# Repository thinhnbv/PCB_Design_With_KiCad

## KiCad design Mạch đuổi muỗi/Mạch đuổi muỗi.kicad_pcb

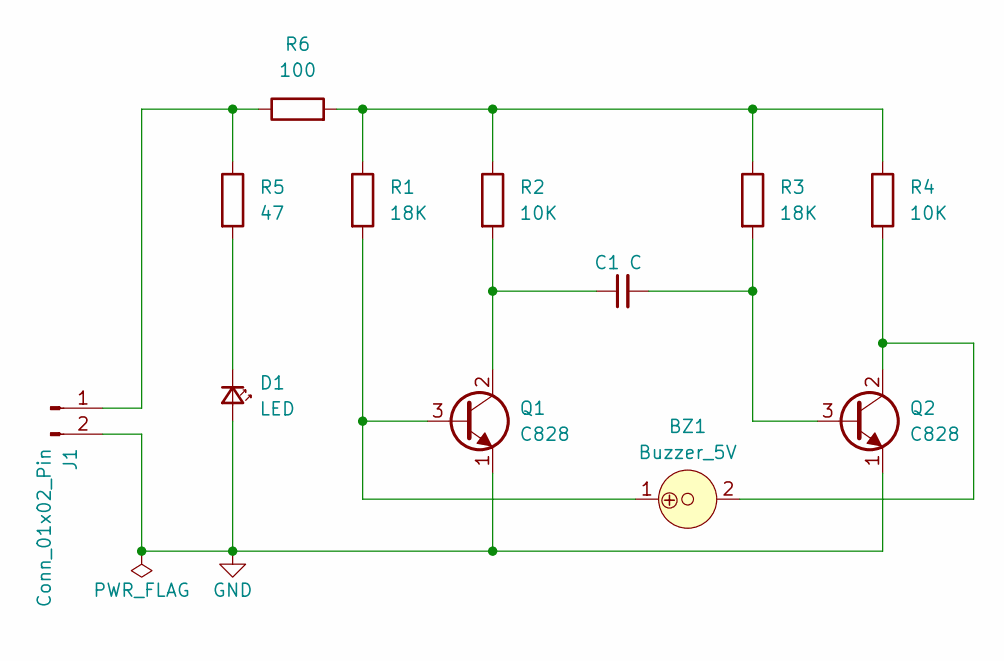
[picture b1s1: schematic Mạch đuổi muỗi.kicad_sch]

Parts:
BZ1: Buzzer_5V; MagneticBuzzer_ProSignal_ABT-410-RC
C1: C; C_Radial_D5.0mm_H5.0mm_P2.00mm; Voltage 1kV; Tolerance 100%
D1: LED; LED_D3.0mm
J1: Conn_01x02_Pin; PinHeader_1x02_P1.27mm_Horizontal
Q1, Q2: C828; TO-92_Inline_Wide
R1, R3: 18K; R_Axial_DIN0207_L6.3mm_D2.5mm_P7.62mm_Horizontal
R2, R4: 10K; R_Axial_DIN0207_L6.3mm_D2.5mm_P7.62mm_Horizontal
R5: 47; R_Axial_DIN0207_L6.3mm_D2.5mm_P7.62mm_Horizontal
R6: 100; R_Axial_DIN0207_L6.3mm_D2.5mm_P7.62mm_Horizontal

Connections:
GND: D1.2 (A), J1.2, Q1.1, Q2.1
unnamed: BZ1.1, Q1.3, R1.2
unnamed: BZ1.2, Q2.2, R4.2
unnamed: C1.1, Q1.2, R2.2
unnamed: C1.2, Q2.3, R3.2
unnamed: D1.1 (K), R5.2
unnamed: J1.1, R5.1, R6.1
unnamed: R1.1, R2.1, R3.1, R4.1, R6.2

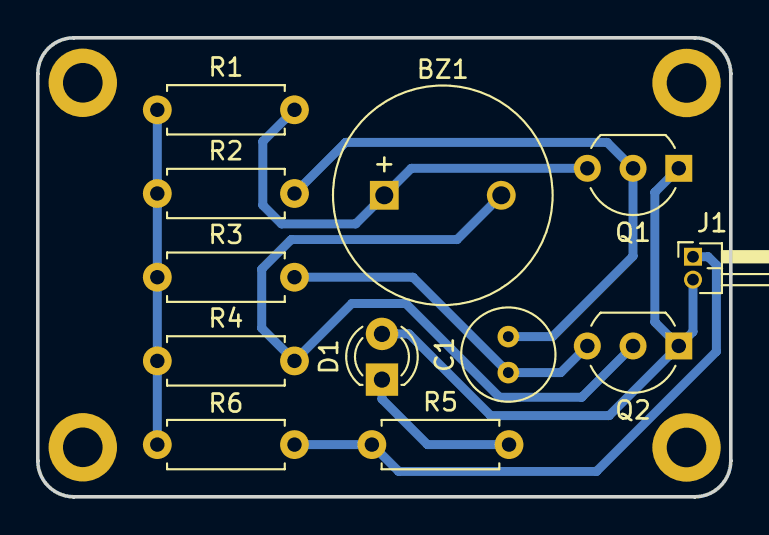
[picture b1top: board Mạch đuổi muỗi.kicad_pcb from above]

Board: 2 copper layers, 38.5 x 25.5 mm, 12 parts (0 on the bottom side), 8 nets.

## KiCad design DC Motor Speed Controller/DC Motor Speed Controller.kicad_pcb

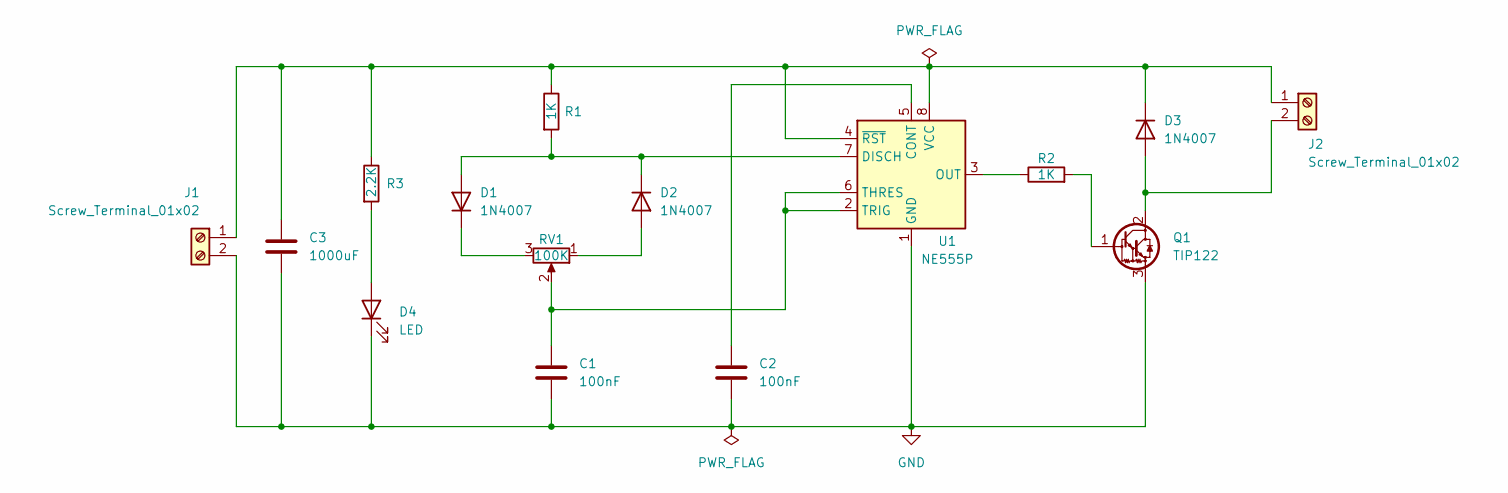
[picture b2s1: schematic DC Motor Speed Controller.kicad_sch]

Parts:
C1, C2: 100nF; C_Disc_D4.7mm_W2.5mm_P5.00mm
C3: 1000uF; CP_Radial_D10.0mm_P5.00mm
D1, D2, D3: 1N4007; D_DO-41_SOD81_P10.16mm_Horizontal
D4: LED; LED_D5.0mm
J1, J2: Screw_Terminal_01x02; TerminalBlock_Phoenix_MKDS-1,5-2_1x02_P5.00mm_Horizontal
Q1: TIP122; TO-220-3_Vertical
R1, R2: 1K; R_Axial_DIN0204_L3.6mm_D1.6mm_P7.62mm_Horizontal
R3: 2.2K; R_Axial_DIN0204_L3.6mm_D1.6mm_P7.62mm_Horizontal
RV1: 100K; Potentiometer_Alps_RK163_Single_Horizontal
U1: NE555P; DIP-8_W7.62mm

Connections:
GND: C1.2, C2.2, C3.2, D4.1 (K), J1.2, Q1.3 (E), U1.1 (GND)
unnamed: D1.2 (A), D2.1 (K), R1.2, U1.7 (DISCH)
unnamed: D1.1 (K), RV1.3
unnamed: D2.2 (A), RV1.1
unnamed: D3.2 (A), J2.2, Q1.2 (C)
unnamed: C3.1, D3.1 (K), J1.1, J2.1, R1.1, R3.1, U1.4 (~RST), U1.8 (VCC)
unnamed: D4.2 (A), R3.2
unnamed: Q1.1 (B), R2.2
unnamed: C2.1, U1.5 (CONT)
unnamed: R2.1, U1.3 (OUT)
unnamed: C1.1, RV1.2, U1.2 (TRIG), U1.6 (THRES)

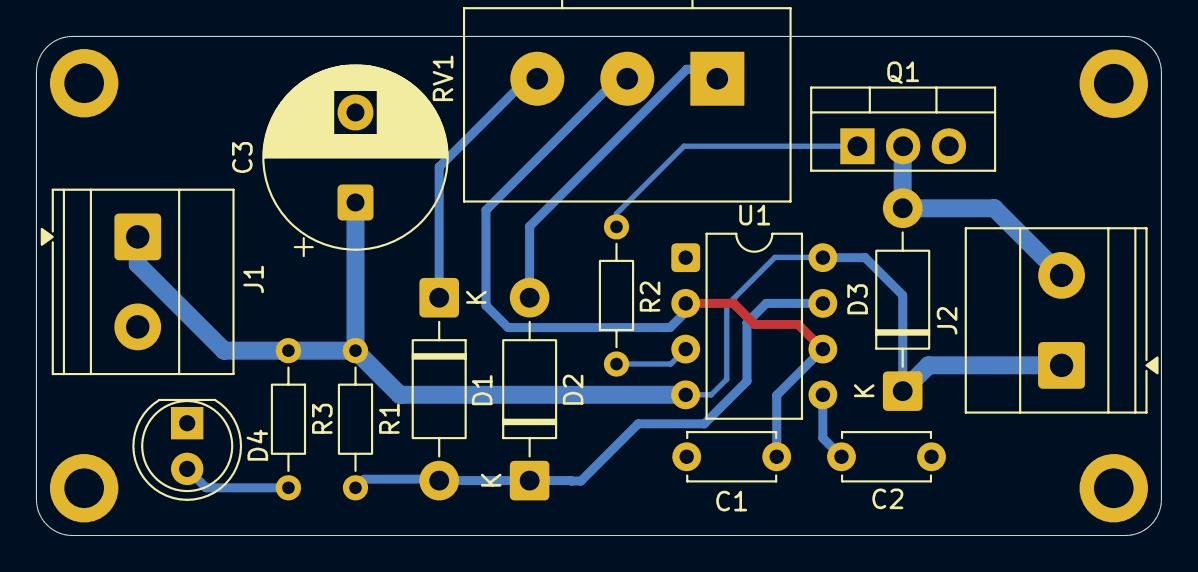
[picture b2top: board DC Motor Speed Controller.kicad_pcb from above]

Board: 2 copper layers, 62.5 x 27.7 mm, 15 parts (0 on the bottom side), 11 nets.

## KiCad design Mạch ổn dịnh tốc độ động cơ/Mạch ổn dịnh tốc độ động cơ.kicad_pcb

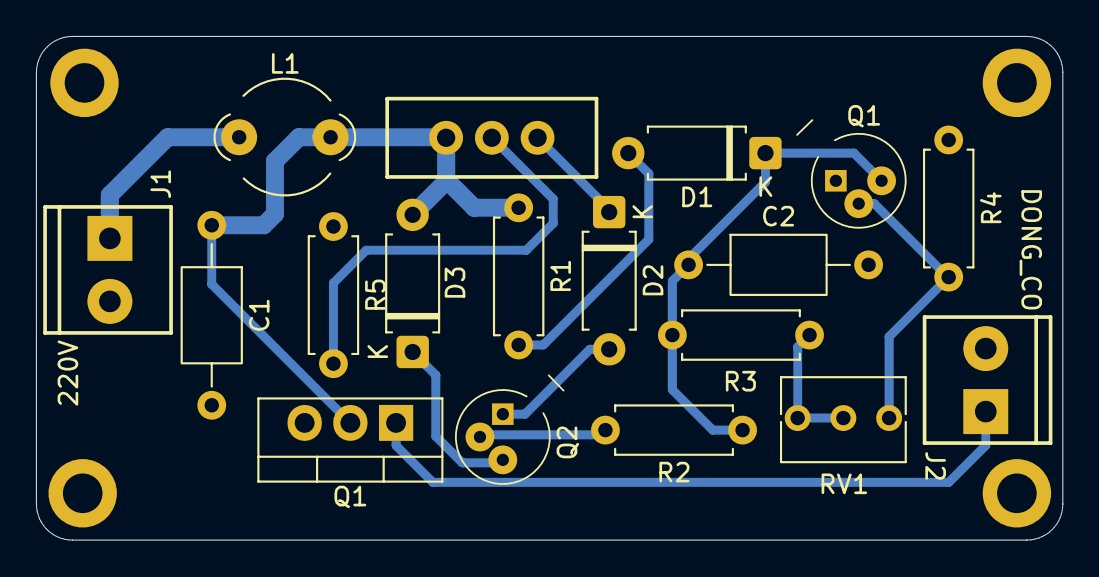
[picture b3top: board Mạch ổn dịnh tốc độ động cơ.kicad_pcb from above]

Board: 2 copper layers, 57.0 x 28.0 mm, 18 parts (0 on the bottom side), 14 nets.

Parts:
C1: 0.1uF/600V; C_Axial_L5.1mm_D3.1mm_P10.00mm_Horizontal
C2: 100uF; C_Axial_L5.1mm_D3.1mm_P10.00mm_Horizontal
D1, D2, D3: D; D_A-405_P7.62mm_Horizontal
J1: 220V; ScrewTerminal_1x02_P3.5mm_Horizontal_Black
J2: DONG_CO; ScrewTerminal_1x02_P3.5mm_Horizontal_Black
L1: L_Ferrite; LairdTech_28C0236-0JW-10
Q1: TIC206; TO-220-3_Vertical
Q1#2, Q2: 2N2222A; TO-18-3
R1: 39K; R_Axial_DIN0207_L6.3mm_D2.5mm_P7.62mm_Horizontal
R2: 68K; R_Axial_DIN0207_L6.3mm_D2.5mm_P7.62mm_Horizontal
R3: 12K; R_Axial_DIN0207_L6.3mm_D2.5mm_P7.62mm_Horizontal
R4: 3.3K; R_Axial_DIN0207_L6.3mm_D2.5mm_P7.62mm_Horizontal
R5: R; R_Axial_DIN0207_L6.3mm_D2.5mm_P7.62mm_Horizontal
RV1: 100K; Potentiometer_Bourns_3266Y_Vertical
SW1: SW_SPDT; Slide_SPDT_PTH_11.6x4.0mm

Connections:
GND: C1.2, C2.2, J1.2, J2.2, Q1#2.1 (E), R4.2
unnamed: D1.2 (A), R1.2
unnamed: C2.1, D1.1 (K), Q1#2.3 (C), R2.1, R3.1
unnamed: D2.2 (A), Q2.1 (E)
unnamed: D2.1 (K), SW1.1 (A)
unnamed: C1.1, D3.2 (A), L1.2, Q1.2 (A2), R1.1, SW1.3 (C)
unnamed: D3.1 (K), Q2.3 (C)
unnamed: J1.1, L1.1
unnamed: J2.1, Q1.1 (A1)
unnamed: Q1.3 (G), R5.1
unnamed: Q1#2.2 (B), R4.1, RV1.1
unnamed: Q2.2 (B), R2.2
unnamed: R3.2, RV1.2, RV1.3
unnamed: R5.2, SW1.2 (B)

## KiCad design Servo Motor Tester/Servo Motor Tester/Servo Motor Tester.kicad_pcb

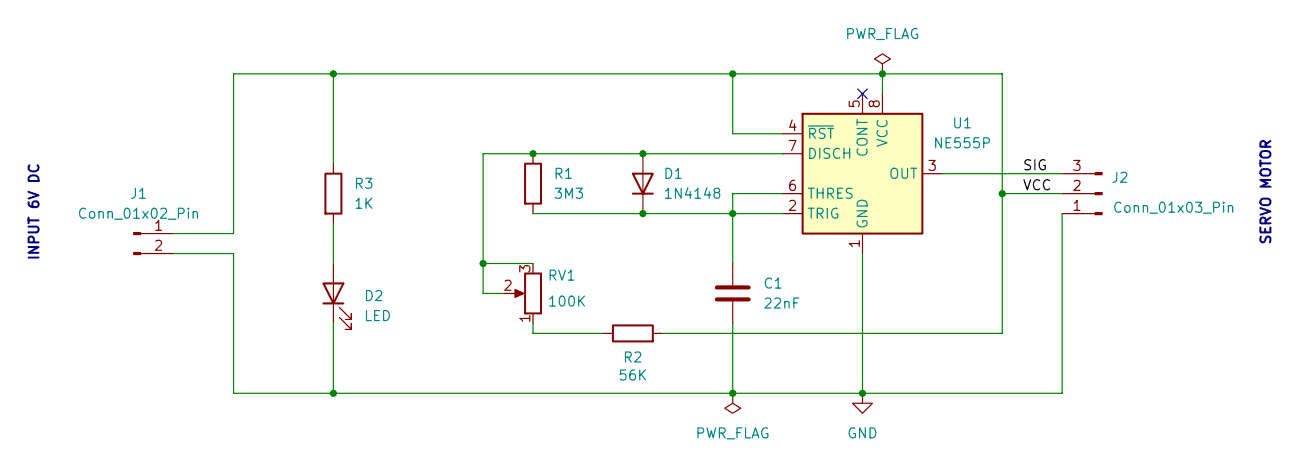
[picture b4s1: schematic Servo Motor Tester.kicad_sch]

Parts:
C1: 22nF; C_Disc_D4.3mm_W1.9mm_P5.00mm
D1: 1N4148; D_DO-35_SOD27_P7.62mm_Horizontal
D2: LED; LED_D3.0mm
J1: Conn_01x02_Pin; PinHeader_1x02_P2.54mm_Horizontal
J2: Conn_01x03_Pin; PinHeader_1x03_P2.54mm_Horizontal
R1: 3M3; R_Axial_DIN0204_L3.6mm_D1.6mm_P7.62mm_Horizontal
R2: 56K; R_Axial_DIN0204_L3.6mm_D1.6mm_P7.62mm_Horizontal
R3: 1K; R_Axial_DIN0204_L3.6mm_D1.6mm_P7.62mm_Horizontal
RV1: 100K; Potentiometer_Alps_RK163_Single_Horizontal
U1: NE555P; DIP-8_W7.62mm

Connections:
/SIG: J2.3, U1.3 (OUT)
/VCC: J1.1, J2.2, R2.2, R3.1, U1.4 (~RST), U1.8 (VCC)
GND: C1.2, D2.1 (K), J1.2, J2.1, U1.1 (GND)
unnamed: D1.2 (A), R1.1, RV1.2, RV1.3, U1.7 (DISCH)
unnamed: C1.1, D1.1 (K), R1.2, U1.2 (TRIG), U1.6 (THRES)
unnamed: D2.2 (A), R3.2
unnamed: R2.1, RV1.1

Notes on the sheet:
SERVO MOTOR
INPUT 6V DC

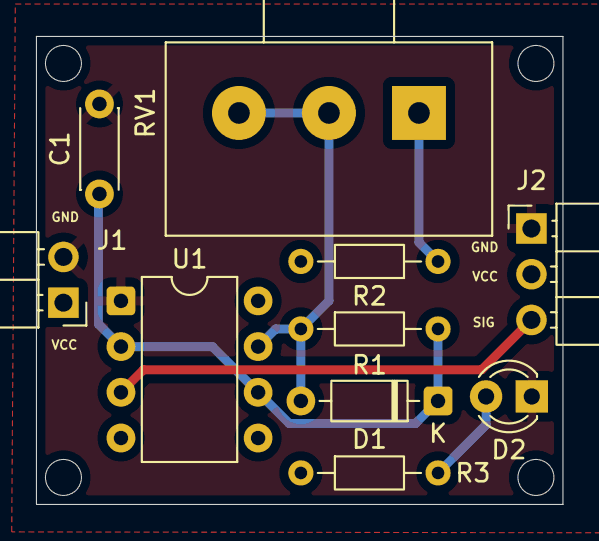
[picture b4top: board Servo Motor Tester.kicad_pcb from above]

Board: 2 copper layers, 29.2 x 26.0 mm, 10 parts (0 on the bottom side), 7 nets.

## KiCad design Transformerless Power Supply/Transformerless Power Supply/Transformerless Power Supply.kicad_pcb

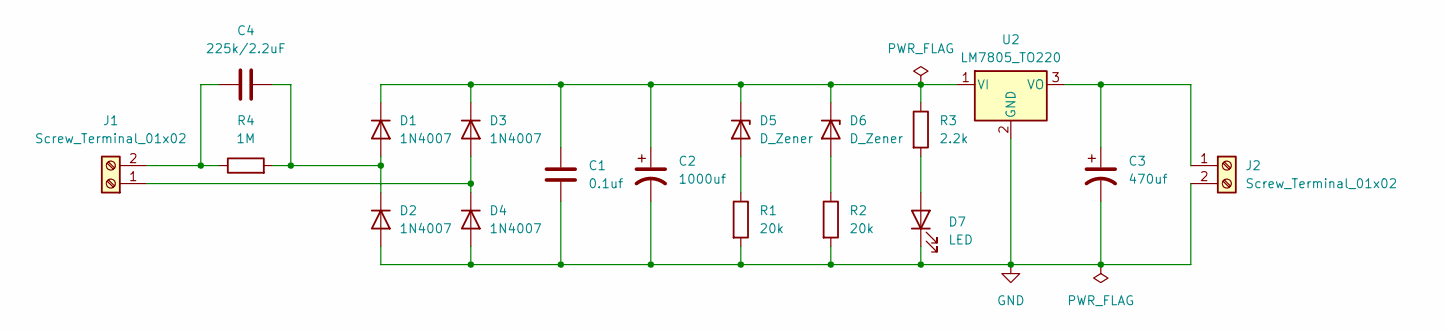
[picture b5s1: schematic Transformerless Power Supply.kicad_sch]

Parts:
C1: 0.1uf; C_Disc_D4.7mm_W2.5mm_P5.00mm
C2: 1000uf; CP_Radial_D10.0mm_P5.00mm
C3: 470uf; CP_Radial_D10.0mm_P3.80mm
C4: 225k/2.2uF; C_Rect_L18.0mm_W6.0mm_P15.00mm_FKS3_FKP3
D1, D2, D3, D4: 1N4007; D_DO-41_SOD81_P10.16mm_Horizontal
D5, D6: D_Zener; D_A-405_P7.62mm_Horizontal
D7: LED; LED_D5.0mm
J1, J2: Screw_Terminal_01x02; TerminalBlock_Phoenix_MKDS-1,5-2-5.08_1x02_P5.08mm_Horizont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
R1, R2: 20k; R_Axial_DIN0207_L6.3mm_D2.5mm_P7.62mm_Horizontal
R3: 2.2k; R_Axial_DIN0207_L6.3mm_D2.5mm_P7.62mm_Horizontal
R4: 1M; R_Axial_DIN0207_L6.3mm_D2.5mm_P7.62mm_Horizontal
U2: LM7805_TO220; TO-220-3_Vertical

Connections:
GND: C1.2, C2.2, C3.2, D2.2 (A), D4.2 (A), D7.1 (K), J2.2, R1.2, R2.2, U2.2 (GND); also elsewhere on the board
unnamed: C4.2, D1.2 (A), D2.1 (K), R4.2
unnamed 2: C1.1, C2.1, D1.1 (K), D3.1 (K), D5.1 (K), D6.1 (K), R3.1, U2.1 (VI); also elsewhere on the board
unnamed: D3.2 (A), D4.1 (K), J1.1
unnamed: D5.2 (A), R1.1
unnamed: D6.2 (A), R2.1
unnamed: D7.2 (A), R3.2
unnamed: C4.1, J1.2, R4.1
unnamed 8: C3.1, J2.1, U2.3 (VO); also elsewhere on the board

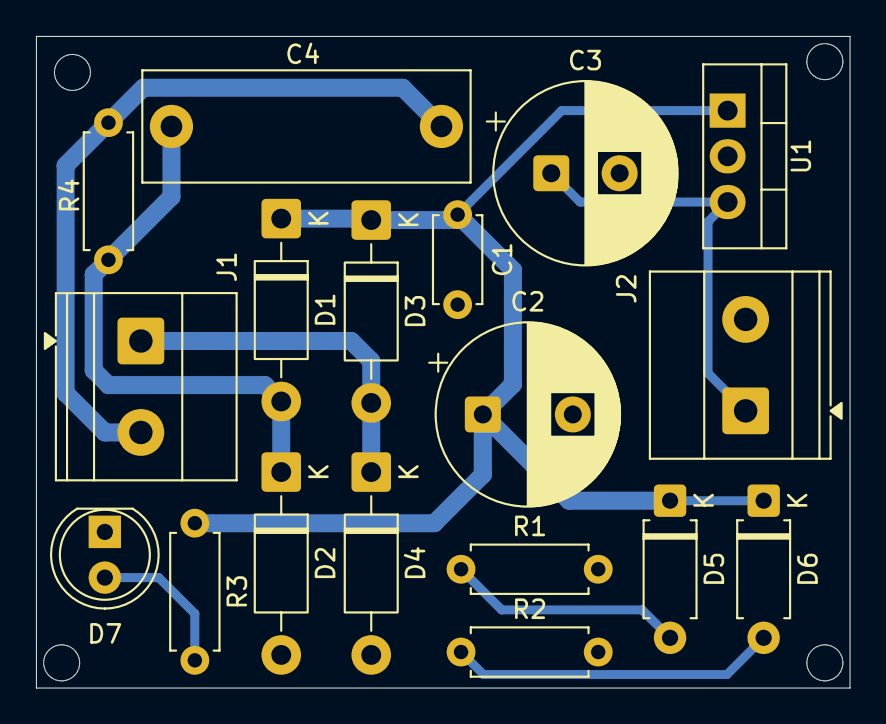
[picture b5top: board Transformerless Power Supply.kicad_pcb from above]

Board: 2 copper layers, 45.2 x 36.2 mm, 18 parts (0 on the bottom side), 9 nets.

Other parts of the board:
U1: LM7805_TO220; TO-220-3_Vertical

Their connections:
GND: U1.2 (GND); also elsewhere on the board
unnamed 2: U1.1 (VI); also elsewhere on the board
unnamed 8: U1.3 (VO); also elsewhere on the board

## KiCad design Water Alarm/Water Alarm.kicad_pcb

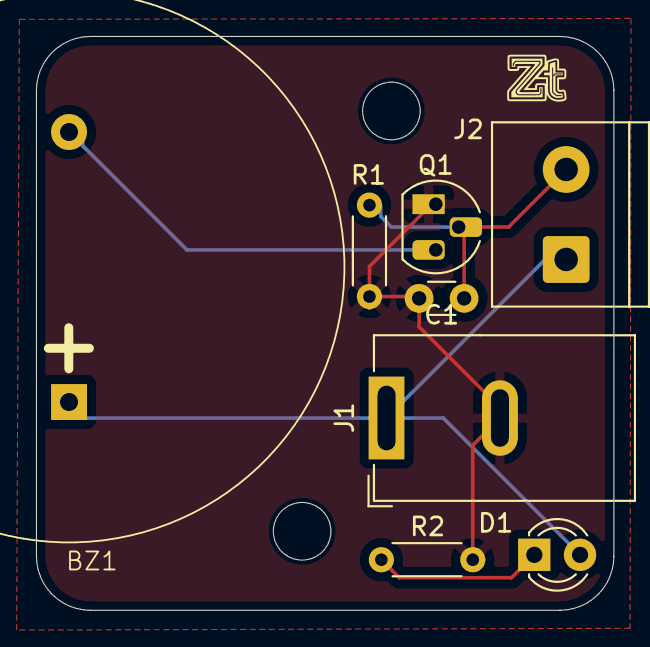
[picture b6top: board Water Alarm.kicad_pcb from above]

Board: 2 copper layers, 32.1 x 31.9 mm, 8 parts (0 on the bottom side), 5 nets.

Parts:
BZ1: Buzzer; Buzzer_D30mm_H20mm_P15mm__668-1652-ND__AI-3035-TT-12V-R
C1: 1nF; C_Disc_D3.0mm_W1.6mm_P2.50mm
D1: LED_Small_Filled; LED_D3.0mm
J1: Jack-DC; BarrelJack_GCT_DCJ200-10-A_Horizontal
J2: Screw_Terminal_01x02; TerminalBlock_Phoenix_PT-1,5-2-5.0-H_1x02_P5.00mm_Horizontal
Q1: 2N7000; TO-92_HandSolder
R1: 10M; R_Axial_DIN0204_L3.6mm_D1.6mm_P5.08mm_Horizontal
R2: 6.8K; R_Axial_DIN0204_L3.6mm_D1.6mm_P5.08mm_Horizontal

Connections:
/Gate: C1.1, J2.2, Q1.2 (G), R1.1
GND: C1.2, J1.2, Q1.1 (S), R1.2, R2.2
unnamed: BZ1.2 (-), Q1.3 (D)
unnamed: D1.1 (K), R2.1
VCC: BZ1.1 (+), D1.2 (A), J1.1, J2.1

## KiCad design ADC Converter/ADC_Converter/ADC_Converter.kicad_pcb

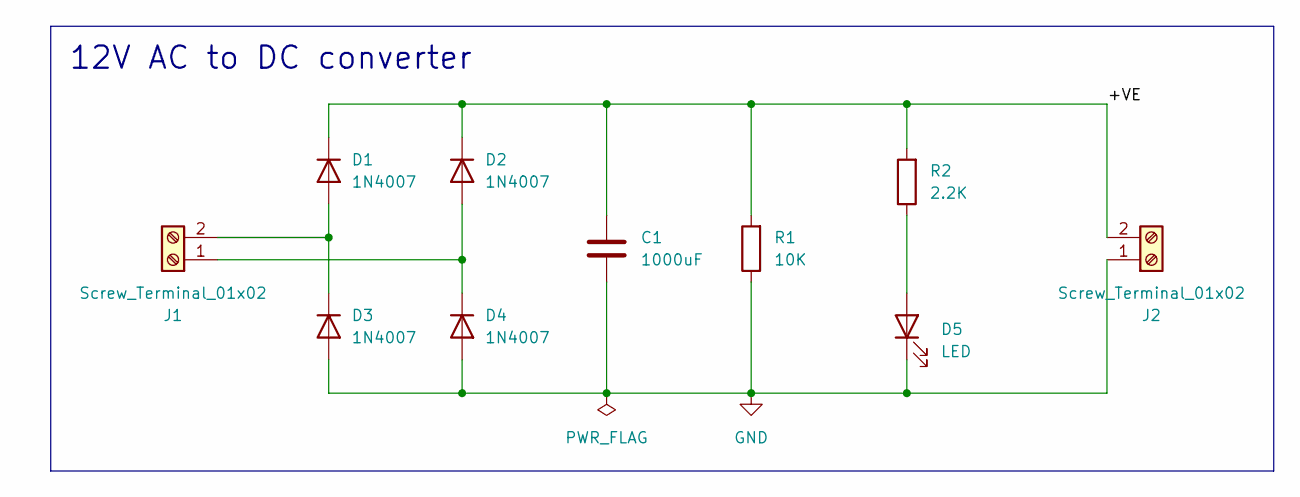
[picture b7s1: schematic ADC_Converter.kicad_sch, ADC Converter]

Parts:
C1: 1000uF; C_Radial_D8.0mm_H11.5mm_P3.50mm
D1, D2, D3, D4: 1N4007; D_DO-41_SOD81_P10.16mm_Horizontal
D5: LED; LED_D5.0mm
J1, J2: Screw_Terminal_01x02; TerminalBlock_Phoenix_MKDS-1,5-2-5.08_1x02_P5.08mm_Horizont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
R1: 10K; R_Axial_DIN0207_L6.3mm_D2.5mm_P7.62mm_Horizontal
R2: 2.2K; R_Axial_DIN0207_L6.3mm_D2.5mm_P7.62mm_Horizontal

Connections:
/+VE: C1.2, D1.1 (K), D2.1 (K), J2.2, R1.2, R2.2
GND: C1.1, D3.2 (A), D4.2 (A), D5.1 (K), J2.1, R1.1
unnamed: D1.2 (A), D3.1 (K), J1.2
unnamed: D2.2 (A), D4.1 (K), J1.1
unnamed: D5.2 (A), R2.1

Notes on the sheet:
12V AC to DC converter

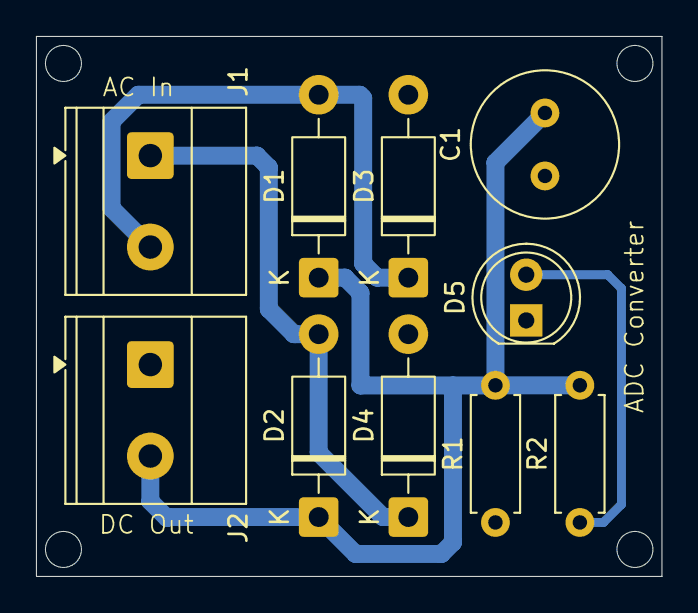
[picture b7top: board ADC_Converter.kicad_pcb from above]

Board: 2 copper layers, 34.8 x 30.0 mm, 10 parts (0 on the bottom side), 5 nets.

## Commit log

2026-05-14 Windows Projects
2026-05-14 Completed
2026-05-16 Final Projects
